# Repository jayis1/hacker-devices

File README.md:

# Hacker Devices — Open Hardware for Security Research

A collection of fully open-source hardware designs for legitimate security research and pentesting. Every device is complete end-to-end: engineering docs, KiCad schematics & PCB layouts, production C/Python firmware, and React Native companion apps. Build it, flash it, run the app, start researching.

## What's Inside Every Device

No half-finished reference designs. Each device folder contains the full stack:

| Category | Files | Description |
|---|---|---|
| **Engineering Docs** | `phase1_conceptual_architecture.md` → `phase4_software_stack.md` | 4-phase design process: requirements, BOM & netlists, PCB layout rules, software stack |
| **KiCad Schematics** | `kicad/*.kicad_pro`, `*.kicad_sch`, `*.kicad_pcb` | Full schematic with real component symbols, net labels, power flags, and board outline with placed footprints |
| **C/Python Firmware** | `firmware/main.c`, `registers.h`, `board.h`, `drivers/`, `Makefile` | Production-quality MCU firmware — init code, drivers with DMA, USB descriptors, wire protocol |
| **React Native App** | `app/App.js`, `screens/`, `components/`, `utils/protocol.js`, `package.json` | Companion mobile app for device control, configuration, real-time status, and data capture |

## Design Methodology

Every device follows a rigorous 4-phase process:

| Phase | Document | Contents |
|---|---|---|
| **Phase 1** | `phase1_conceptual_architecture.md` | Purpose, performance targets, constraints, block diagram, bus topology, power domains |
| **Phase 2** | `phase2_component_selection_schematics.md` | BOM with real part numbers, pinouts/MUX tables, decoupling networks, netlists, impedance matching |
| **Phase 3** | `phase3_pcb_blueprints_layout.md` | PCB stackup, routing rules, length matching, via strategy, thermal management, DFM notes |
| **Phase 4** | `phase4_software_stack.md` | MMIO/register defs, clock & GPIO init (production C), critical device driver, device tree, bootloader |

## Devices

| # | Device | Status | Description |
|---|---|---|---|
| 1 | [`wifi-pentest-dongle/`](wifi-pentest-dongle/) | ✅ Complete | 802.11ax monitor/inject, deauth, PMKID capture |
| 2 | [`rf-transceiver-tool/`](rf-transceiver-tool/) | ✅ Complete | Sub-GHz + 2.4GHz multi-protocol (CC1101 + nRF24) |
| 3 | *badusb-injector* | ⏳ Queued | HID emulation payload injector, multi-profile |
| 4 | *nfc-rfid-cloner* | ⏳ Queued | 13.56MHz + 125kHz, Mifare/EM4100 |
| 5 | *network-tap-mitm* | ⏳ Queued | 2× GbE transparent bridge, packet capture |
| 6 | *can-bus-analyzer* | ⏳ Queued | OBD-II + CAN-FD, automotive pentest |
| 7 | *sdr-keyfob-replay* | ⏳ Queued | 433/315MHz keyfob capture & replay |
| 8 | *ble-sniffer-spoofer* | ⏳ Queued | nRF52, advertisement inject, GATT fuzz |
| 9 | *imsi-catcher-detector* | ⏳ Queued | LTE/4G SDR analysis |
| 10 | *biometric-bypass-toolkit* | ⏳ Queued | Fingerprint emulation, RFID clone for access control |

## Constraints

- **BOM target:** Under $100 per device
- **Form factor:** Portable, USB-powered or battery-operated
- **All designs use real, purchasable components** with exact part numbers
- **KiCad schematics are valid KiCad 7+ format** — open them directly
- **Firmware is production-quality C** — not stubs or pseudocode
- **React Native apps have working UI** with proper state management and wire protocol matching the firmware

## License

| Component | License |
|---|---|
| Hardware design (KiCad) | CERN-OHL-S v2 |
| C firmware & drivers | GPL-2.0 |
| Python tools & scripts | MIT |
| React Native companion apps | MIT |

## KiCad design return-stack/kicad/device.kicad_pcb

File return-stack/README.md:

# Return Stack — Released-Resource Free-List Head Witness

Author and creator: jayis1. Hardware revision A. Protocol RS1, policy revision 1.

Status: unbuilt engineering prototype. This package contains target-linked C firmware, a working Linux desktop application, and native routed KiCad carrier sources. Software and CAD checks are recorded in VERIFICATION.md. Fabrication, physical programming, electrical qualification, calibrated timing and actual target interoperability have not been performed. The device is an observer of a diagnostic contract, not an allocator, protection mechanism, security certificate or safety interlock.

Original firmware, application and tests: GPL-2.0-only. Original hardware utilities: MIT. Original carrier design: CERN-OHL-S-2.0. Purchased modules, installed tools and standard KiCad footprints retain their upstream provenance and licenses.

## Purpose and practical value

Return Stack investigates whether a resource recycler actually returns freed identities to the head of its free list. An embedded service can maintain correct occupancy while corrupting the ordering of its available descriptors. A cancellation path that appends rather than prepends, a stale cached head, or a completion handler that substitutes numeric priority can silently select the wrong free resource. Ordinary successful-request counts will not expose that difference. Return Stack retains return order independently and freezes its evidence at the first admission inconsistent with the declared list.

A practical target is an owner-instrumented embedded security service with four reusable request descriptors, audit buffers or context slots. The owner exports committed admissions and releases over a slow diagnostic adapter. Harmless workloads exercise normal completion, cancellation, complete drain and immediate resubmission. The observer checks which identity is reused without collecting pointers, credentials, addresses, packet payloads or resource contents. A source-level trace and independent waveform capture should establish that the adapter faithfully represents the suspected defect.

Last-return-first reuse is not intrinsically secure or insecure. Its usefulness depends on the target's documented allocation contract. A locality-oriented implementation may intentionally reuse its most recently returned descriptor; a hardened implementation may intentionally do the opposite. Applying this observer to the latter would produce meaningless findings. Security impact, including stale-state reuse or broken cleanup expectations, needs separate confirmation. This instrument proves neither erasure nor isolation and does not turn a policy mismatch into an exploit.

## Exact measurement contract

The pool contains four exclusive resource identities, zero through three. At experimental start, all identities are free and their free-list order, head first, is zero, one, two, three. ALLOCATE reports an admission already committed by the target. The selected identity must be free and must equal the current head. Accepting the operation removes that head. Selecting an occupied identity is a duplicate allocation; selecting a different free identity is a free-list-head bypass. A full pool has no admissible allocation.

RELEASE reports the completed return of an occupied identity. The observer clears that identity's occupancy and pushes it onto the front of the free list. Any occupied identity may return at any time; release order is unrestricted. An unoccupied identity cannot be returned again and produces an orphan-release fault. There is no nested-call return discipline, mandatory release rank, fairness rotation, minimum reuse delay or requirement to visit every identity.

The implementation represents ordering with return ordinals rather than a mutable linked list. Each successful release increments the global completed count and stores that ordinal against its identity. The eligible free identity has the greatest retained return ordinal; never-returned identities tie at zero and are ordered numerically. Occupied identities are excluded from the comparison. Every accepted admission separately retains its admission ordinal and cumulative use count, but those quantities do not choose the free-list head.

For example, allocate zero, release zero, allocate zero is legal even though three identities have never been used. Allocate zero and one, release zero and then one: the next eligible identity is one, not zero. Reallocate one, then zero: both operations are legal. After filling all four slots, release three and then one: the next allocation must be one even though three has the greater numeric identity. Complete drain preserves return ordering; it does not restore the virgin numeric list. Idle time does not change priority.

At the first rejected semantic or interface observation, interpretation stops permanently for that run. The previous coherent occupancy and histories remain available. The rejected observation is counted without pretending that the target rejected its own operation. Eligibility displayed after a halt refers to the retained observer model, not the actual target state or permission to continue testing. Export the evidence, inspect the target and harness, and establish a fresh controlled baseline before resetting the observer.

## Distinction from existing devices and provenance

The synchronized jayis1/hacker-devices repository was inventoried by device directory and README content. Closely related contracts were read rather than comparing names alone. Lowest Fit chooses the minimum numeric free identity and explicitly ignores return order. Cursor Fit advances a cyclic search cursor on admission, not release. Oldest Free chooses the least-recently admitted free identity. Context Stack constrains nested returns and allows equal-tag reentrancy; Return Stack has unique resources, arbitrary return order and constrained subsequent admission. These contracts accept different operation traces.

The return-stack directory was recovered from an interrupted execution of this same authorized task after its provenance was confirmed in the originating task history. Fresh target builds, host tests and application tests were run; inherited build products were not treated as evidence. The passive carrier, register map, startup, qualification, CRC, bounded UART and desktop transport reuse jayis1-authored repository infrastructure. UQ-prefixed C identifiers are retained internal platform names, whereas RS1 identifies this device on the wire.

The original contribution is the integrated diagnostic instrument: released-resource ordering, independent literal-list oracle, return-ordinal evidence, sparse-history checks, companion display and operating procedure. Free-list stacks themselves are established engineering, and the resistor circuit is intentionally conventional. No worldwide novelty, patentability or new electronics topology claim is made. Runtime files are self-contained within this folder. There is no shared systems tree, unified CLI, external server dependency or import from daily-ideas.

## Attack surface, threat model and authorized use

Use only on equipment you own or have explicit written authorization to assess. Scope must cover enclosure access, target instrumentation, attachment points, approved workloads, service interruption, restoration and evidence retention. Permission for network scanning does not imply permission to attach wires or alter diagnostic firmware. Begin on a low-energy laboratory fixture with production dependencies and consequential outputs disconnected.

The investigated attack surface is resource bookkeeping: cancellation queues, completion identity, stale head pointers, double returns, duplicate admissions and fast-path versus recovery-path policy differences. Authorized red teams can ask an owner to expose a suspected allocator regression through harmless operations. Researchers can compare implementation revisions under identical reduced traces. Penetration testers can repeat an approved reproduction after remediation and attach the retained finding to their report. The device itself generates no target workload, sends no commands, transmits no radio signals and performs no exploitation.

The trusted base includes the diagnostic adapter, operator, MCU image, purchased development board, wiring and workstation. A malicious adapter can fabricate every indication or omit inconvenient events. A compromised host can rewrite exports. Physical programming access can replace the firmware. The CRC detects accidental corruption, not forgery, authentication failure or replay. There is no secure boot, signed updater, persistent boot identifier, trusted wall clock, encrypted storage or attested evidence. Treat timing and use counts as potentially sensitive engagement data even though payloads are absent.

Receive-only describes the supplied firmware and application, not a certified hardware data diode. The GPIOs could become outputs under replacement firmware. Input loading, ground loops, shorts and back-power can disturb an attached target even without intentional transmission. Do not connect to mains-referenced equipment, unknown field wiring, vehicles, medical devices, occupied access controls or hazardous machinery. Stop immediately if attachment changes behavior. The legal disclaimer does not replace electrical qualification or informed operator supervision.

## Hardware specification and bill of materials

The active module is an external ST NUCLEO-F401RE with STM32F401RET6 Cortex-M4, 512 KiB flash and 96 KiB SRAM. The firmware assumes reset-default nominal 16 MHz HSI and derives a nominal one-millisecond SysTick. USART2 transmits 115200 baud, eight data bits, no parity and one stop bit through PA2 to ST-LINK's USB virtual COM interface. The purchased module supplies regulation, decoupling, USB connection, reset, SWD and programming access. These are external module facilities, not imaginary circuits omitted from a standalone MCU schematic.

The custom carrier is a cable-connected, two-layer 80 by 70 mm PCB with nominal 1.6 mm thickness and 0.3 mm tracks. It contains fourteen through-hole components, thirty pads and nine nets. There is no FPGA, radio, antenna, battery, charger, analog sensor, removable storage, isolated power supply or target power output. It is not a mechanically stacking Arduino shield. Provide nonconductive supports, underside protection and strain relief; mounting holes and enclosure CAD are not supplied.

| Reference | Quantity | Selection |
| --- | --- | --- |
| External module | 1 | ST NUCLEO-F401RE, purchased revision checked before use |
| R1, R3, R5, R7 | 4 | Yageo MFR-25FBF52-100K, 100 kOhm, 1%, axial |
| R2, R4, R6, R8 | 4 | Yageo MFR-25FBF52-1K, 1 kOhm, 1%, axial |
| J1, J3, J4, J5, J6 | 5 | Harwin M20-9990245, 1x2, 2.54 mm vertical header |
| J2 | 1 | Harwin M20-9990445, 1x4, 2.54 mm vertical header |
| Harness and support | 1 set | Short labelled insulated leads and insulating base |

Verify body dimensions, drilled-hole fit, resistor lead forming and mating connector polarity against purchased parts before fabrication. Resistor footprints are DIN0207 with 7.62 mm lead spacing. Supplier stock and cost have not been checked. Reserve a conservative 5 V, 500 mA USB source allowance for the external module as planning headroom, not measured consumption or USB-compliance evidence. The passive carrier has no supply rail and cannot power the target.

| Signal | Target contact | MCU contact | Nucleo connector | Sample bit |
| --- | --- | --- | --- | --- |
| TAG0 | J3.1 | J2.1 | CN8.1 / A0 / PA0 | 0 |
| TAG1 | J4.1 | J2.2 | CN8.2 / A1 / PA1 | 1 |
| ALLOCATE | J5.1 | J2.3 | CN8.3 / A2 / PA4 | 2 |
| RELEASE | J6.1 | J2.4 | CN8.4 / A3 / PB0 | 3 |

Every target connector's second pin is ground. Both J1 pins are ground, never supply inputs. J2 carries only signals; connect module ground separately through J1. Each target `_IN` net passes through a 1 kOhm series resistor to its MCU node, with 100 kOhm from that node to ground. Disconnected wires appear low and cannot be distinguished from legitimate low indications. No cable-integrity monitoring is provided.

Only known common-ground push-pull signals between zero and 3.3 V are within the proposed interface. Exclude 5 V, 1.8 V, negative, differential and unknown-voltage sources. The series resistors are not isolation, dedicated ESD protection or surge suppression. There are no level translators or external clamps. Validate ground offset, loading, leakage, thresholds and harness capacitance on the assembled fixture. Power the observer before enabling target outputs, and remove target signals before depowering it. USB and target grounds become common.

Manufacturer references are ST UM1724, particularly the NUCLEO-F401RE connector table and USART bridge configuration; RM0368 for peripherals; and the STM32F401xD/xE datasheet for electrical limits. UM1724 specifies the default VCP connection with SB13/SB14 on and SB62/SB63 off. Check the actual module revision rather than assuming those bridges remain factory configured. Reference: https://www.st.com/resource/en/user_manual/dm00105823-stm32-nucleo-64-boards-mb1136-stmicroelectronics.pdf .

## Architecture and block diagram

```text
Owned diagnostic adapter         Passive carrier          External Nucleo
TAG0 ------------------------------ 1k --+---------------- PA0
TAG1 ------------------------------ 1k --+---------------- PA1
ALLOCATE -------------------------- 1k --+---------------- PA4
RELEASE --------------------------- 1k --+---------------- PB0
                                         | each MCU node
                                        100k
                                         |
Target ground -------------------------- GND ------------- module GND

GPIO -> continuity check -> bundled tag / independent strobe qualification
     -> tag setup and opposite-strobe guards -> free-list-head comparison
     -> transactional occupancy + admission/return ordinals -> RS1 encoder
     -> USART2 TX -> ST-LINK USB serial -> Ledger / History / Integrity
```

Internal target-facing GPIO pulls are disabled. PA and PB are read separately, so the acquisition is not atomic across ports. The instrument is a slow diagnostic observer, not a native-speed bus analyzer. An adapter must export committed events in order without silently overflowing its own queue. Instrumentation can perturb the behavior under study; document that uncertainty and corroborate a finding outside the observer.

## Firmware design and timing decisions

The C11 image has no RTOS, heap allocation, filesystem, command parser or downloaded vendor SDK dependency. Startup initializes data and BSS and supplies core vectors. The linker maps flash at 0x08000000 and SRAM at 0x20000000 with explicit stack headroom. Board support initializes input GPIO, reset-cause capture, SysTick, USART2 and the independent watchdog. USART reception remains disabled. The main loop samples on advancing ticks, services at most one UART byte per iteration and offers status every nominal 100 ms when the transmit queue permits.

Qualification treats the two tag bits as one bundle and the strobes independently. A changed candidate needs three subsequent matching samples before qualification. This prevents separately settled tag bits from synthesizing an unintended identity, while unrelated chatter cannot postpone the other strobe forever. Before an accepted strobe rise, the qualified tag requires five prior stable observations. Raw and qualified tag values must agree at the edge, and the opposite strobe must be low in the relevant raw and qualified observations. Simultaneous qualified operations are ambiguous and rejected.

Use conservative laboratory waveforms: both strobes low, set the tag and hold it for at least twelve nominal milliseconds; assert exactly one strobe for at least six milliseconds; return it low for at least six milliseconds while retaining the tag. These are fixture recommendations, not calibrated electrical specifications. A pulse shorter than the qualification window may disappear entirely. The observer does not measure every raw transition and cannot guarantee detection of sub-sample glitches. Start with both strobes low and the target's list explicitly reset; quiet wires alone do not establish the baseline.

Any advancing timestamp delta other than one tick halts correlation with an acquisition-gap fault. Repeated calls at the same timestamp do nothing. Ordinary unsigned timer wrap is supported. Counter updates occur on a speculative ledger copy; if an increment would overflow, the sample's accounting is discarded and the last committed state is retained with an exhaustion fault. The watchdog starts through bounded status waits; initialization failure is a terminal finding. A hard fault after watchdog activation should cause a reset, but physical watchdog recovery has not been tested.

The transmit queue is bounded to 768 bytes. Submission refuses empty, oversized or overlapping frames. Polling never waits for UART readiness and abandons a queued frame at its 100 ms timeout, recording a transport diagnostic. Status time can continue advancing after a halt while measurement fields remain frozen. Therefore fresh serial reception does not imply valid ongoing acquisition. No host command clears history. Reset is a new experiment, not automatic authorization to forget an interrupted target lifetime.

## Wire protocol and companion application

Frames are ASCII `RS1,TYPE,decimal,...*HHHH` followed by LF. The checksum is CRC-16/CCITT with polynomial 0x1021, initial 0xffff, no reflection and no final XOR, over the ASCII bytes preceding the asterisk. TYPE B carries captured reset flags. TYPE P carries the exact policy tuple `3,1,5,4,0,1`: qualifier, nominal sample interval, setup requirement, resource count, initial head and policy revision. Policy repeats about once per second to support late attachment without emitting false reset notifications.

TYPE S contains, in order: now, levels, valid, halted, faults, phase, active, depth, stable, observed, rounds, attempts, launched, completed, rejected, gaps, missed, queued, peak, use0 through use3, stamp0 through stamp3, ret0 through ret3, and tx_fail. All are unsigned 32-bit values. The first fault is sticky: bit values 1, 2, 4, 8, 16, 32 and 64 mean head bypass, orphan return, duplicate admission, interface ambiguity, acquisition gap, counter exhaustion and watchdog startup failure respectively. WAIT is phase zero; TRACK is one. A halt clears qualification validity without deleting retained evidence.

The Linux application uses Python's standard tkinter and termios facilities rather than a mobile framework because direct local serial inspection is the intended workflow. Run `/usr/bin/python3 return-stack/app/console.py` from the repository root. New live opens the selected tty read-only at 115200 baud, flushes queued input and begins a new host session. Disconnect restores terminal attributes and preserves evidence. A second connection is refused until the first closes. No target configuration or firmware-update controls exist; the policy is fixed and announced explicitly.

Ledger displays the counters, current occupied identities, eligible head and fault description. History retains up to 256 accepted snapshots. Integrity shows source, live-versus-replay provenance, parser errors, reset metadata, age, frozen-session reasons and transport failures. Replay accepts only regular files up to two MiB; FIFOs and devices are refused. Export JSON creates a new file with private mode 0600, refuses overwrite and final-component symlinks, and includes author jayis1 plus provenance and integrity metadata. It does not upload data or encrypt exports.

The parser bounds framing, validates checksums, enforces the exact policy and rejects impossible endpoint accounting. Admission counts equal returns plus occupancy; per-resource uses sum to admissions; return ordinals must belong to actual returned resources. Across snapshots, return and admission stamps cannot migrate without matching operations. An identity that stayed free with no admissions blocks reuse of initially lower-priority free identities. An initially occupied identity may legitimately return and become the head, so endpoint eligibility alone must not reject that hidden sequence.

These are necessary sparse-history checks, not a complete reconstruction proof. A compromised source can forge plausible records. Two advancing snapshots are needed before transport is considered live. Duplicate timestamps do not refresh age; contradictory duplicates, rollback, disappearing faults and changed halted evidence freeze interpretation. A long reception pause or excessive host/device progress divergence requires explicit reconnect rather than treating backlog as current. Some resets remain indistinguishable without a persistent boot identifier, and oscillator drift can cause conservative reconnection. Replay is never labelled live.

## Build, verification and supervised bring-up

Required tools are GNU Arm Embedded GCC with newlib/nosys support, host GCC, Make, Python 3 with tkinter, KiCad 9 and its system Python pcbnew module. Xvfb supports display-backed tests on a headless machine. No pip, npm or network package installation is required by the application. From the repository root run:

```sh
make -C return-stack/firmware clean all test
xvfb-run -a /usr/bin/python3 -m unittest discover -s return-stack/tests -v
/usr/bin/python3 return-stack/tools/check_hardware.py
/usr/bin/python3 return-stack/tools/check_release.py
```

The target build emits ELF, binary and map under ignored firmware/build. The hardware generator is a maintenance command, `/usr/bin/python3 return-stack/tools/generate_hardware.py`, that rewrites only this device's CAD outputs and manifest. Back up intentional CAD edits before using it. The hardware checker runs ERC and DRC, exports a fresh XML netlist, and compares references, values, footprints and every pad/net assignment against the PCB and saved connectivity manifest. Passing those checks does not validate an external supply or unmodelled harness.

Host tests compare operation sequences against an independent literal free-list oracle, including every release permutation, immediate reuse, duplicate/orphan faults, overlap, setup guards, timestamp wrap and exhaustion. Serial tests exercise bounds, timeout and recovery; main-loop tests cover lost boot telemetry, periodic late-attach policy and watchdog-start failure. Application tests feed the real C encoder's synthetic records through validation and actual GUI screens, use Linux PTYs for connection/hangup paths, and verify private exports and evidence retention. Synthetic fixtures are not physical measurements.

Before assembly, inspect the rendered schematic, board routing, connector numbering and actual BOM dimensions. With power removed, check continuity against the netlist and absence of shorts. Connect only the observer module first. Program the ELF with a supervised ST-LINK/SWD tool suitable for the purchased module; there is no automatic flash target or claimed programming result in this release. Check reset defaults, current consumption, serial framing and input levels before attaching an owned test fixture. Confirm each tag and strobe independently with a scope, then replay the documented legal and deliberately invalid diagnostic traces at slow rates.

Record module revision, firmware revision, wiring, target instrumentation revision, baseline free-list order and observed limitations with each experiment. Export before resetting either side. A repeated fault should be minimized to a short trace and checked against source logs and independent waveforms. A missing fault is not evidence of general memory safety: hidden operations, lying instrumentation, narrow pulses, disconnected wires and untested resource paths remain outside the assurance provided. Retain exports only for the authorized engagement and delete them under its agreed policy.

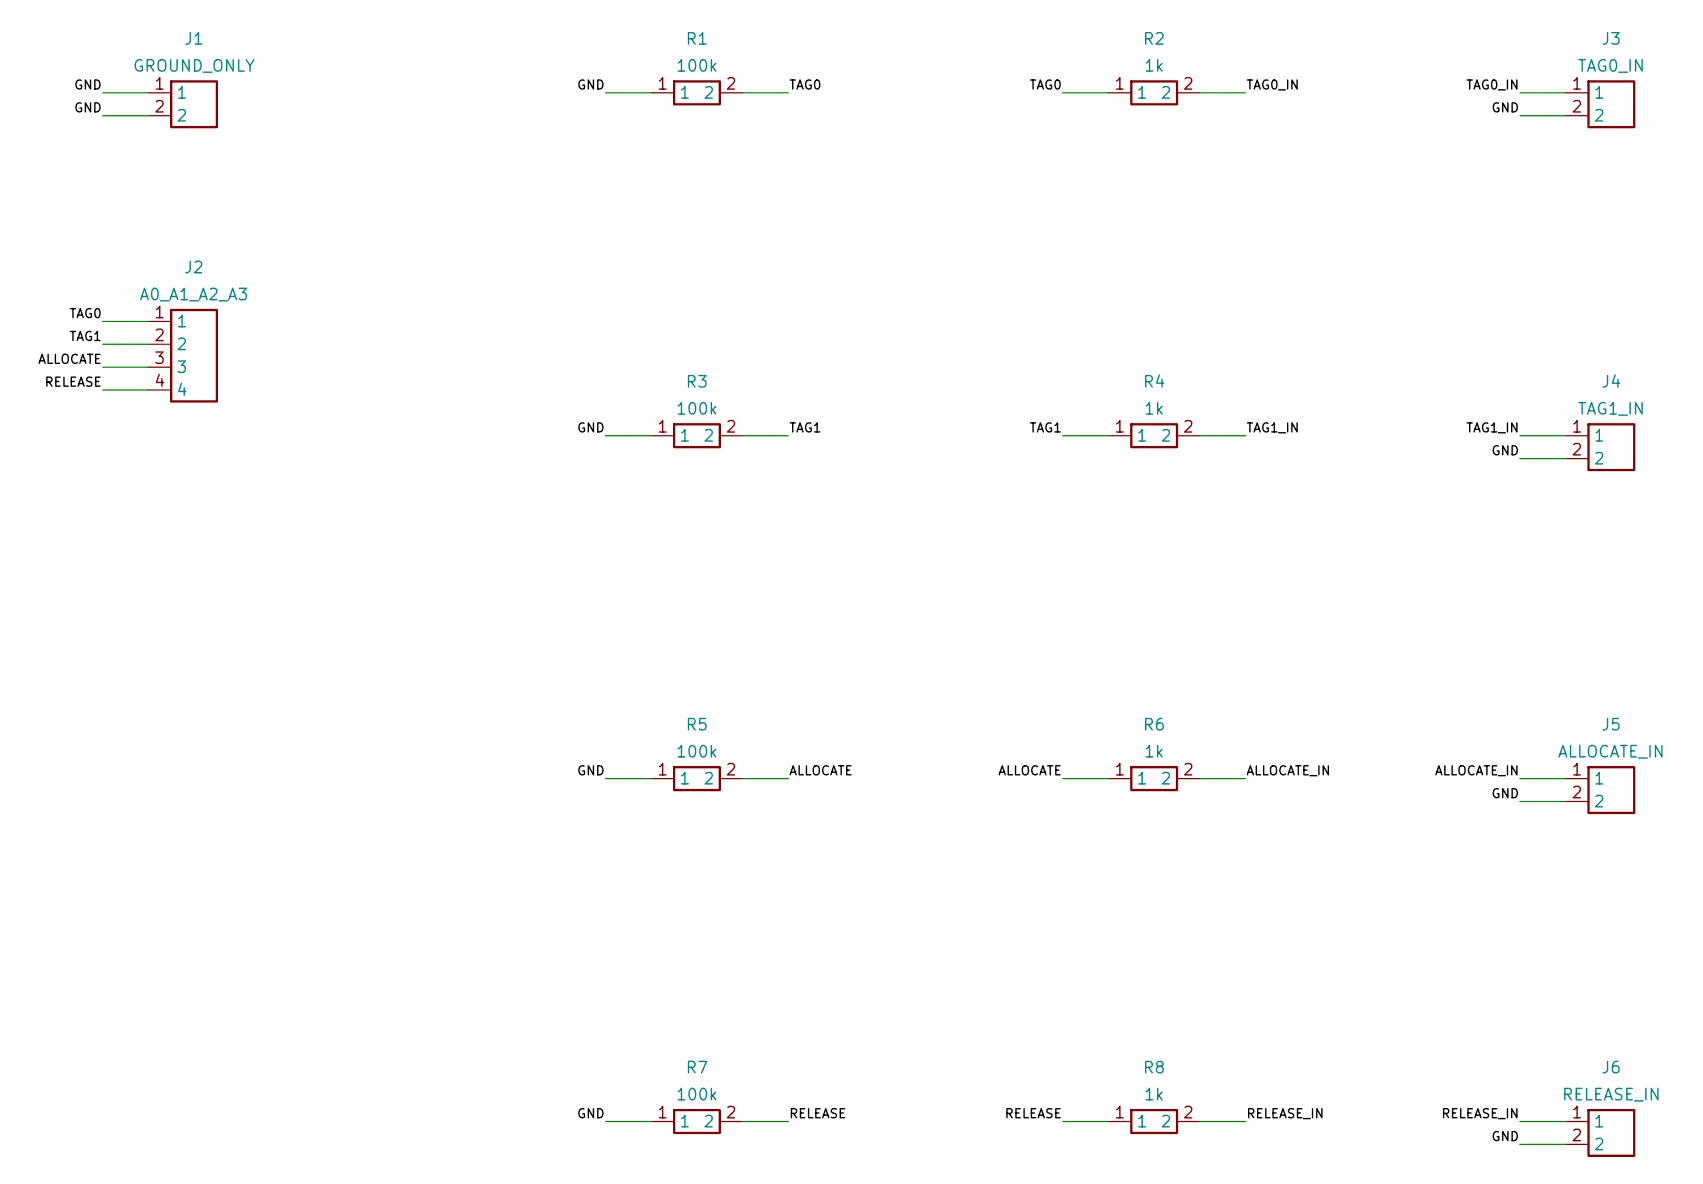
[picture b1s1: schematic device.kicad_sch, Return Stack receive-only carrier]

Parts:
J1: GROUND_ONLY; PinHeader_1x02_P2.54mm_Vertical
J2: A0_A1_A2_A3; PinHeader_1x04_P2.54mm_Vertical
J3: TAG0_IN; PinHeader_1x02_P2.54mm_Vertical
J4: TAG1_IN; PinHeader_1x02_P2.54mm_Vertical
J5: ALLOCATE_IN; PinHeader_1x02_P2.54mm_Vertical
J6: RELEASE_IN; PinHeader_1x02_P2.54mm_Vertical
R1, R3, R5, R7: 100k; R_Axial_DIN0207_L6.3mm_D2.5mm_P7.62mm_Horizontal
R2, R4, R6, R8: 1k; R_Axial_DIN0207_L6.3mm_D2.5mm_P7.62mm_Horizontal

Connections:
ALLOCATE: J2.3, R5.2, R6.1
ALLOCATE_IN: J5.1, R6.2
GND: J1.1, J1.2, J3.2, J4.2, J5.2, J6.2, R1.1, R3.1, R5.1, R7.1
RELEASE: J2.4, R7.2, R8.1
RELEASE_IN: J6.1, R8.2
TAG0: J2.1, R1.2, R2.1
TAG0_IN: J3.1, R2.2
TAG1: J2.2, R3.2, R4.1
TAG1_IN: J4.1, R4.2

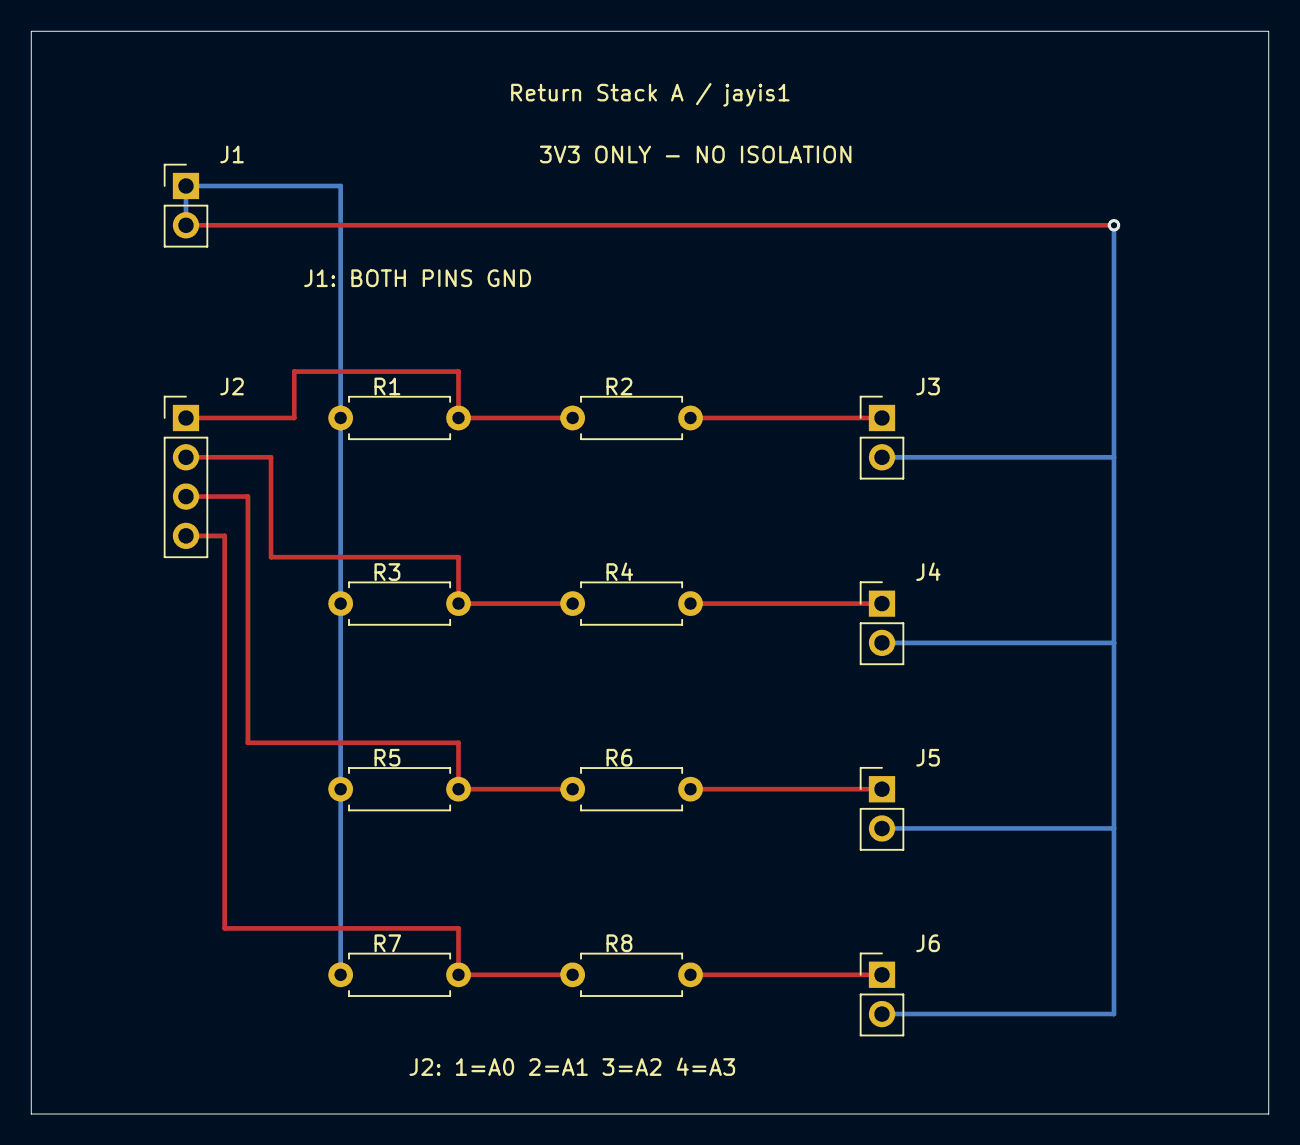
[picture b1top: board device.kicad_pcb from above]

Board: 2 copper layers, 80.0 x 70.0 mm, 14 parts (0 on the bottom side), 9 nets.

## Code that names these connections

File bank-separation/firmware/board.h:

/* Author: jayis1. SPDX-License-Identifier: GPL-2.0-only */
#ifndef BS_BOARD_H
#define BS_BOARD_H
#include <stdbool.h>
#include <stddef.h>
#include <stdint.h>
#define CORE_HZ 16000000u
#define SERIAL_BAUD 115200u
#define SERIAL_BUFFER 768u
/* TAG0 PA0; TAG1 PA1; ALLOCATE PA4; RELEASE PB0. */
void board_init(void);
uint8_t board_levels(void);
uint32_t board_millis(void);
uint32_t board_reset_flags(void);
bool board_watchdog_start(void);
void board_watchdog_feed(void);
bool serial_submit(const char *data, size_t size);
void serial_poll(void);
bool serial_busy(void);
bool serial_take_timeout(void);
#endif

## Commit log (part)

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2026-06-12 Initial commit — wifi-pentest-dongle (phases 1-3), root README
2026-06-12 Update README — open everything: KiCad schematics, C/Python firmware, React Native apps
2026-06-13 Add rf-transceiver-tool — full design with KiCad, firmware, and companion app
    - STM32F401CCU6 Cortex-M4 MCU at 84 MHz
    - CC1101 Sub-GHz (300-928 MHz) transceiver via SPI1+DMA
    - nRF24L01+ 2.4 GHz transceiver via SPI2
    - SSD1306 128x64 OLED display via I2C1
    - USB CDC virtual serial for host communication
    - Production C firmware with DMA-backed SPI drivers
2026-06-13 wifi-pentest-dongle: add Phase 4, KiCad, firmware, and React Native app
    Phase 4: Software stack — JH7110 MMIO registers, clock/GPIO init, AX210 PCIe
    monitor mode driver (DMA rings, channel hopping, frame injection), USB CDC-ECM+ACM
    composite gadget, device tree overlay, U-Boot SPL board init
    KiCad: Full schematic (SoC, DDR, WiFi M.2, PMIC, USB-C, eMMC, TPM, battery charger,
    LEDs, antennas), PCB (85x35mm, 6-layer HDI, impedance-controlled net classes)
    Firmware: main.c (SPL entry, PMIC init, clock config), board.h, registers.h,
2026-06-14 feat: add Substation - Sub-GHz IoT Gateway Implant
    New hacker device for multi-protocol Sub-GHz security research:
    - CC1352P SoC with ARM Cortex-M4F @ 48 MHz
    - Multi-protocol: Zigbee, Z-Wave, Sub-GHz OOK/FSK/GFSK, BLE 5.0
    - 64 MB SDRAM capture buffer, 16 MB SPI Flash
    - ATECC608A hardware crypto (secure boot, BLE auth)
    - USB-C data+charge, MicroSD, SMA external antenna
2026-06-14 feat: add PHANTOM - USB HID emulation payload injector
2026-06-14 feat: add CAN Bus Infiltrator — dual-channel automotive CAN security research tool
    Complete design for a pocket-sized OBD-II CAN bus analyzer:
    - Phase 1: Conceptual architecture with dual CAN channels, galvanic isolation,
    BLE 5.0 wireless control, USB-C CDC, and microSD logging
    - Phase 2: Full BOM (~9.55 @ 100u), pinout tables for STM32F407VGT6,
    nRF52840, TJA1050, ISO1050, netlists with source→component→dest routing
    - Phase 3: 4-layer PCB (65×35mm), impedance-controlled CAN/USB diff pairs,
2026-06-14 feat: add NFC Relay Phantom — multi-protocol NFC/RFID security research platform
    Dual-MCU design (STM32L4S5 + NRF52832) with PN5180 NFC frontend
    and EM4095 125 kHz RFID reader. Supports ISO 14443A/B, FeliCa,
    ISO 15693 sniffing/emulation, EM4100/HID Prox cloning to T5577,
    BLE relay attack between paired devices, and Mifare Classic attacks.
    - Phase 1-4 architecture docs with full BOM, pinouts, netlists
    - KiCad project with 4-layer PCB, dual onboard antennas
2026-06-14 feat: add ShadowTap — PoE stealth network tap & MITM implant
    Complete production-quality design for a palm-sized, PoE-powered inline
    Ethernet tap and MITM implant for authorized red-team engagements.
    - Phase 1: Conceptual architecture (dual ENET, cut-through, MITM engine, BLE C2)
    - Phase 2: BOM (~5), full pinout tables, netlists, decoupling, impedance pairs
    - Phase 3: 4-layer PCB stackup, RGMII/diff pair routing, thermal management,
    isolation barriers, GND strategy
2026-06-15 feat: add BLE Phantom — dual BLE 5.x security research platform
    - STM32F401CCU6 main MCU with dual nRF52832 BLE radios
    - USB-A dongle form factor (80×40mm), <00 BOM (~4)
    - 4-layer PCB with impedance-controlled RF and USB routing
    - SPI command protocol for radio communication with CRC16
    - USB CDC virtual serial for host app communication
    - 7 operating modes: Idle, Sniff, Scan, Advertise, Connect, MITM, Replay
2026-06-15 feat: add USB DMA Phantom — Thunderbolt/USB4 DMA attack platform
    Complete hardware design for a pocket-sized Thunderbolt/USB4 DMA security
    research platform. Key features:
    - STM32F423CHU6 Cortex-M4F MCU @ 120 MHz
    - TI XIO2001 PCIe-to-PCI bridge with DMA engine
    - TI HD3SS460 USB-C alternate mode mux for TBT/USB4
    - nRF52832 BLE 5.0 for encrypted C2 (AES-256-CTR)
2026-06-15 Add Volt-Glitcher: High-precision fault injection tool
2026-06-15 feat: rewrite volt-glitcher — full production-quality design
2026-06-15 feat: add eMMC Flash Dumper — forensic flash acquisition platform
    Complete production-quality design for a portable hardware platform
    that performs direct, hardware-level extraction of raw flash memory
    from eMMC 5.1, ONFI NAND, and SPI NOR devices.
    Key specs:
    - STM32H743VI Cortex-M7 @ 480 MHz + iCE40UP5K FPGA
    - 512 MB DDR3L buffer, USB 3.0 SuperSpeed, microSD standalone
2026-06-16 Add CAN Creeper: dual CAN FD sniffer & injector for automotive security research
    - nRF52840 + 2x MCP2518FD + 2x TJA1445 CAN FD transceivers
    - 8MB QSPI PSRAM frame buffer, 16MB NOR Flash storage
    - BLE 5.2 NUS + USB CDC-ACM dual transport
    - 128x64 SSD1306 OLED display
    - React Native companion app with sniffer, injector, scripts, settings
    - Full KiCad schematic (300+ lines), PCB layout, 4-layer stackup
2026-06-16 Add PCIe Screamer: PCIe DMA attack device (in-progress)
2026-06-16 Add README.md for PCIe Screamer
2026-06-16 Fix author credit: change Nous Research to jayis1
2026-06-16 Add sata-phantom: SATA bus interposer for transparent storage bus MITM, frame inspection, injection, and covert exfiltration
2026-06-16 Add spectre-sniffer: portable EM side-channel analysis and Tempest surveillance device
    Spectre-Sniffer is a novel handheld device for electromagnetic side-channel
    analysis, Tempest (van Eck phreaking) surveillance, and cryptographic key
    extraction via DPA/CPA. Features:
    - Wideband RF frontend (10 MHz - 8 GHz) with LNA, tunable filter, downconverter
    - 16-bit 130 MSPS ADC (LTC2208) with Lattice iCE40UP5K FPGA for real-time FFT
    - ESP32-S3 application processor with 2.8" TFT touchscreen
2026-06-17 Add hdmi-siphon: transparent HDMI interposer for video security research, frame capture, EDID/HDCP manipulation, CEC bus monitoring, and covert recording
2026-06-17 Add forge-probe: Silicon Backdoor Debug Probe — FPGA-accelerated JTAG/SWD/cJTAG platform for hardware security research and silicon debug
2026-06-17 Add silent-symphony: ultrasonic covert channel communicator for air-gap exfiltration research
2026-06-17 Add fiber-phantom: Covert fiber optic network tap & MITM implant with 3 deployment modes (bend-tap, inline-couple, SFP+ pass-through)
2026-06-18 Add gnss-phantom: portable GNSS/GPS signal spoofing & simulation platform for security research
2026-06-18 Add ghostbus: covert SWD/JTAG hardware debug implant with BLE backhaul
2026-06-18 Add trace-reaper: portable power-side-channel analyzer with on-device FPGA CPA
2026-06-19 Add powerline-reaper: Powerline Communications (PLC/HomePlug AV) network interception & injection tool
2026-06-19 Add photon-strike: portable laser fault injection platform with on-device AES DFA solver
2026-06-22 Add wire-reaper: multi-bus embedded peripheral infiltrator (I2C/SPI/UART/1-Wire sniffer, injector, emulator)
2026-06-23 Add acoustic-phantom: portable acoustic side-channel emanation capture & analysis appliance
2026-06-24 Add lora-phantom: LoRaWAN & LoRa infiltration device with SX1262 sniff/replay/inject/fuzz
2026-06-25 Add uwb-phantom: Ultra-Wideband ranging & digital-key manipulation tool
2026-06-26 Add sideprobe: portable power & EM side-channel cryptanalysis platform
2026-06-27 Add tactile-phantom: covert touch-controller bus MITM implant (I2C/SPI tap + inject)
2026-06-28 Add thermal-phantom: precision thermal fault injection & side-channel analysis device
2026-06-29 Add coil-grip: Wireless Power Transfer (Qi) MITM, contactless glitch & covert channel platform
2026-06-30 Add zigbee-phantom: IEEE 802.15.4/Zigbee attack platform with key recovery, rogue coordinator & selective jamming
